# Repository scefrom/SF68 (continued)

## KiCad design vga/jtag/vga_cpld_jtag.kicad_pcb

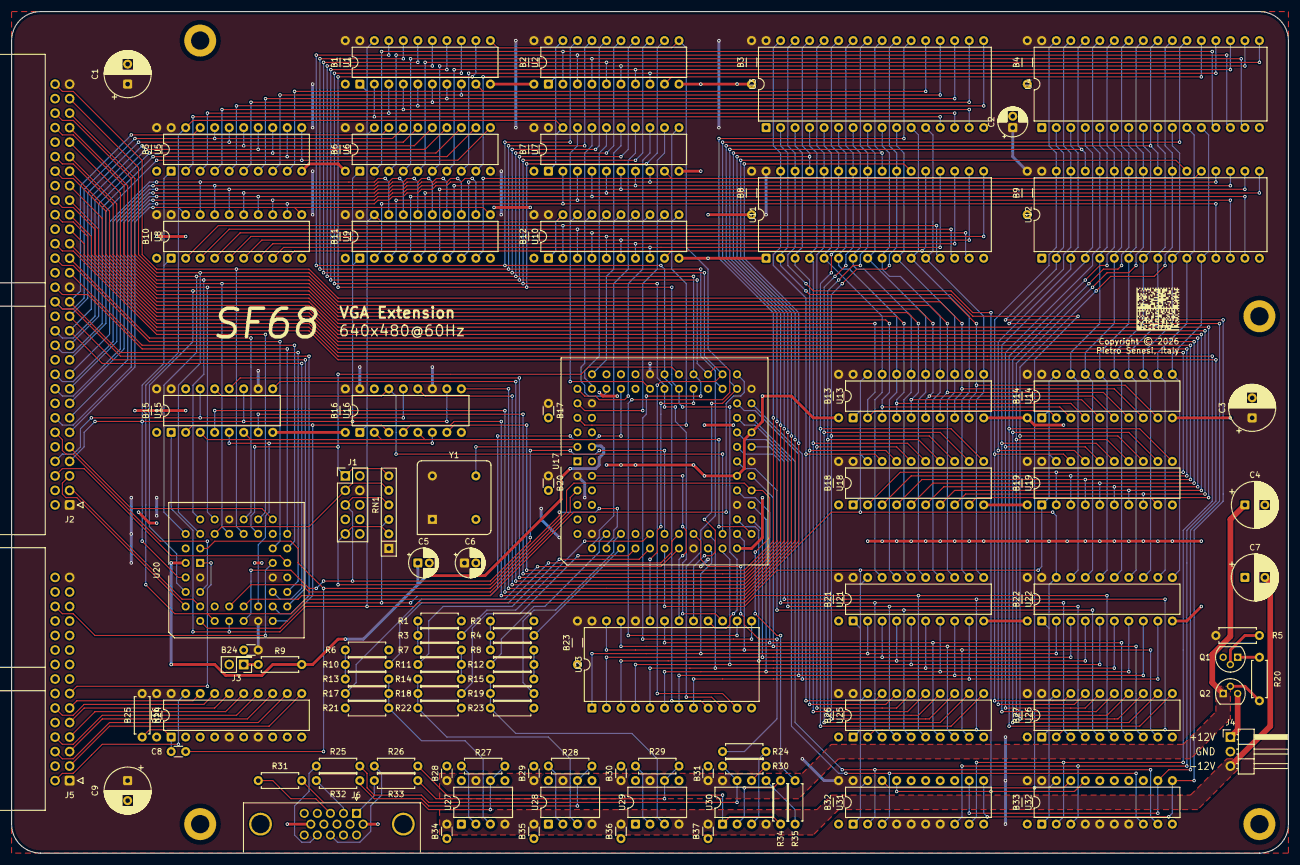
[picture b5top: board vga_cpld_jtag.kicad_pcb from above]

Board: 2 copper layers, 223.5 x 147.3 mm, 127 parts (0 on the bottom side), 229 nets.

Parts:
B1, B2, B3, B4, B5, B6, B7, B8, B9, B10, B11, B12, B13, B14, B15, B16, B18, B19, B21, B22, B23, B25, B26, B27, B32, B33: 100n; C_Disc_D3.0mm_W1.6mm_P7.62mm
B17, B20, B24, B28, B29, B30, B31, B34, B35, B36, B37: 100n; C_Disc_D3.0mm_W1.6mm_P2.54mm
C1, C3, C4, C7, C9: 100u; CP_Radial_D8.0mm_P3.50mm
C2, C5, C6: 10u; CP_Radial_D5.0mm_P2.00mm
C8: 22p; C_Disc_D3.0mm_W1.6mm_P2.54mm
J1: jtag; PinHeader_2x05_P2.54mm_Vertical
J2: perslota; IDC-Header_2x30_P2.54mm_Horizontal
J3: oe1_12v_bypass; PinHeader_2x01_P2.54mm_Vertical
J4: vgasupply; PinHeader_1x03_P2.54mm_Horizontal
J5: perslotb; IDC-Header_2x15_P2.54mm_Horizontal
J6: DE15_Socket_HighDensity; DSUB-15-HD_Socket_Horizontal_P2.29x1.90mm_EdgePinOffset3.03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
M1, M2, M3, M4: MountingHole_3.2mm_M3_DIN965_Pad
Q1: Q_NPN_CBE; TO-92
Q2: Q_PNP_CBE; TO-92
R1, R2, R3, R4, R6, R10, R11, R12, R17, R18, R19, R20: 5.4k; R_Axial_DIN0207_L6.3mm_D2.5mm_P7.62mm_Horizontal
R5: 10k; R_Axial_DIN0207_L6.3mm_D2.5mm_P7.62mm_Horizontal
R7, R8, R13, R14, R15: 2.7k; R_Axial_DIN0207_L6.3mm_D2.5mm_P7.62mm_Horizontal
R9, R24, R30, R34, R35: 1k; R_Axial_DIN0207_L6.3mm_D2.5mm_P7.62mm_Horizontal
R16: 4.7k; R_Axial_DIN0207_L6.3mm_D2.5mm_P7.62mm_Horizontal
R21, R22, R23: 800; R_Axial_DIN0207_L6.3mm_D2.5mm_P7.62mm_Horizontal
R25, R26: 50; R_Axial_DIN0207_L6.3mm_D2.5mm_P7.62mm_Horizontal
R27, R28, R29: 620; R_Axial_DIN0207_L6.3mm_D2.5mm_P7.62mm_Horizontal
R31, R32, R33: 33; R_Axial_DIN0207_L6.3mm_D2.5mm_P7.62mm_Horizontal
RN1: 10k; R_Array_SIP6
U1, U2, U7, U10, U13, U14, U18, U19, U21, U22, U25, U26, U31, U32: 74AHC541; DIP-20_W7.62mm
U3, U4, U11, U12: AS6C4008-55PCN; DIP-32_W15.24mm
U5, U6, U8, U9: 74HC245; DIP-20_W7.62mm
U15, U16: 74HC157; DIP-16_W7.62mm
U17: ATF1508AS-xJx84; PLCC-84_THT-Socket
U20: ATF1502AS-xJx44; PLCC-44_THT-Socket
U23: AT28C16; DIP-24_W15.24mm
U24: 74HC541; DIP-20_W7.62mm
U27, U28, U29: LM6171xxN; DIP-8_W7.62mm
U30: LM6172; DIP-8_W7.62mm
Y1: CXO_DIP8_25.175MHz; Oscillator_DIP-8

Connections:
+5V: B1.1, B2.1, B3.1, B4.1, B5.1, B6.1, B7.1, B8.1, B9.1, B10.1, B11.1, B12.1, B13.1, B14.1, B15.1, B16.1, B17.1, B18.1, B19.1, B20.1, B21.1, B22.1, B23.1, B24.1, B25.1, B26.1, B27.1, B32.1, B33.1, C1.1, C2.1, C3.1, C6.1, C9.1, J1.4, J2.1, J2.31, J2.59, J5.1, J5.29, R5.1, R16.1, RN1.1 (common), U1.20 (VCC), U2.20 (VCC), U3.32 (VCC), U4.32 (VCC), U5.20 (VCC), U6.20 (VCC), U7.20 (VCC), U8.20 (VCC), U9.20 (VCC), U10.20 (VCC), U11.32 (VCC), U12.32 (VCC), U13.20 (VCC), U14.20 (VCC), U15.10 (I1c), U15.16 (VCC), U16.11 (I0c), U16.16 (VCC), U17.3 (VCC_INT), U17.13 (VCC_IO), U17.26 (VCC_IO), U17.38 (VCC_IO), U17.43 (VCC_INT), U17.53 (VCC_IO), U17.66 (VCC_IO), U17.78 (VCC_IO), U18.20 (VCC), U19.20 (VCC), U20.3 (VCC), U20.15 (VCC), U20.23 (VCC), U20.35 (VCC), U21.20 (VCC), U22.20 (VCC), U23.21 (~WE), U23.24 (VCC), U24.5 (A3), U24.7 (A5), U24.20 (VCC), U25.20 (VCC), U26.20 (VCC), U31.4 (A2), U31.5 (A3), U31.6 (A4), U31.7 (A5), U31.20 (VCC), U32.4 (A2), U32.5 (A3), U32.6 (A4), U32.7 (A5), U32.20 (VCC), Y1.1 (EN), Y1.8 (Vcc)
/08to02: RN1.3 (R2), U17.71 (I/O/TDO), U20.7 (I/O/TDI)
/AC.~P: J5.26, U20.25 (I/O/PD2)
/ADR_{0}: U17.51 (I/O), U21.9 (A7), U22.9 (A7), U23.8 (A0)
/ADR_{1}: U17.52 (I/O), U21.8 (A6), U22.8 (A6), U23.7 (A1)
/ADR_{2}: U17.37 (I/O), U21.7 (A5), U22.7 (A5), U23.6 (A2)
/ADR_{3}: U17.29 (I/O), U21.6 (A4), U22.6 (A4), U23.5 (A3)
/ADR_{4}: U17.30 (I/O), U21.5 (A3), U22.5 (A3), U23.4 (A4)
/ADR_{5}: U17.36 (I/O), U21.4 (A2), U22.4 (A2), U23.3 (A5)
/ADR_{6}: U17.35 (I/O), U21.3 (A1), U22.3 (A1), U23.2 (A6)
/ADR_{7}: U17.28 (I/O), U21.2 (A0), U22.2 (A0), U23.1 (A7)
/ADR_{8}: U17.34 (I/O), U23.23 (A8), U25.9 (A7), U26.9 (A7)
/ADR_{9}: U17.41 (I/O), U23.22 (A9), U25.8 (A6), U26.8 (A6)
/ADR_{10}: U17.40 (I/O), U23.19 (A10), U25.7 (A5), U26.7 (A5)
/ADR_{11}: U17.22 (I/O), U25.6 (A4), U26.6 (A4)
/ADR_{12}: U17.44 (I/O), U25.5 (A3), U26.5 (A3)
/ADR_{13}: U17.48 (I/O), U25.4 (A2), U26.4 (A2)
/ADR_{14}: U17.46 (I/O), U25.3 (A1), U26.3 (A1)
/ADR_{15}: U17.45 (I/O/PD2), U25.2 (A0), U26.2 (A0)
/ADR_{16}: U17.49 (I/O), U31.2 (A0), U32.9 (A7)
/ADR_{17}: U17.50 (I/O), U31.3 (A1), U32.8 (A6)
/A_{1}: J2.60, U13.9 (A7), U14.9 (A7), U20.34 (I/O)
/A_{2}: J2.57, U13.8 (A6), U14.8 (A6), U20.41 (I/O/GCLK3)
/A_{3}: J2.55, U13.7 (A5), U14.7 (A5), U20.40 (I/O)
/A_{4}: J2.56, U13.6 (A4), U14.6 (A4), U20.39 (I/O)
/A_{5}: J2.53, U13.5 (A3), U14.5 (A3), U20.36 (I/O)
/A_{6}: J2.54, U13.4 (A2), U14.4 (A2), U20.37 (I/O)
/A_{7}: J2.51, U13.3 (A1), U14.3 (A1), U20.4 (I/O)
/A_{8}: J2.49, U13.2 (A0), U14.2 (A0)
/A_{9}: J2.50, U18.9 (A7), U19.9 (A7)
/A_{10}: J2.47, U18.8 (A6), U19.8 (A6)
/A_{11}: J2.48, U18.7 (A5), U19.7 (A5)
/A_{12}: J2.45, U18.6 (A4), U19.6 (A4)
/A_{13}: J2.43, U18.5 (A3), U19.5 (A3)
/A_{14}: J2.44, U18.4 (A2), U19.4 (A2)
/A_{15}: J2.41, U18.3 (A1), U19.3 (A1)
/A_{16}: J2.42, U18.2 (A0), U19.2 (A0)
/A_{17}: J2.39, U31.9 (A7), U32.2 (A0)
/A_{18}: J2.37, U31.8 (A6), U32.3 (A1)
/A_{19}: J2.38, U20.31 (I/O)
/A_{20}: J2.35, U20.33 (I/O)
/A_{21}: J2.36, U20.27 (I/O)
/A_{22}: J2.33, U20.26 (I/O)
/A_{23}: J2.32, U20.28 (I/O)
/BE.~IO: J2.12, U20.5 (I/O)
/BE.~M: J2.9, U20.29 (I/O)
/CLK: U17.83 (I/GCLK1), Y1.5 (OUT)
/CM: U17.5 (I/O), U20.12 (I/O)
/DAT_{0}: U1.18 (Y0), U2.18 (Y0), U17.64 (I/O), U23.9 (D0)
/DAT_{1}: U1.17 (Y1), U2.17 (Y1), U17.57 (I/O), U23.10 (D1)
/DAT_{2}: U1.16 (Y2), U2.16 (Y2), U17.56 (I/O), U23.11 (D2)
/DAT_{3}: U1.15 (Y3), U2.15 (Y3), U17.60 (I/O), U23.13 (D3)
/DAT_{4}: U1.14 (Y4), U2.14 (Y4), U17.58 (I/O), U23.14 (D4)
/DAT_{5}: U1.13 (Y5), U2.13 (Y5), U17.65 (I/O), U23.15 (D5)
/DAT_{6}: U1.12 (Y6), U2.12 (Y6), U17.63 (I/O), U23.16 (D6)
/DAT_{7}: U1.11 (Y7), U2.11 (Y7), U17.55 (I/O), U23.17 (D7)
/DAT_{8}: U7.18 (Y0), U10.18 (Y0), U17.67 (I/O)
/DAT_{9}: U7.17 (Y1), U10.17 (Y1), U17.73 (I/O)
/DAT_{10}: U7.16 (Y2), U10.16 (Y2), U17.76 (I/O)
/DAT_{11}: U7.15 (Y3), U10.15 (Y3), U17.74 (I/O)
/DAT_{12}: U7.14 (Y4), U10.14 (Y4), U17.12 (I/O/PD1)
/DAT_{13}: U7.13 (Y5), U10.13 (Y5), U17.75 (I/O)
/DAT_{14}: U7.12 (Y6), U10.12 (Y6), U17.77 (I/O)
/DAT_{15}: U7.11 (Y7), U10.11 (Y7), U17.79 (I/O)
/DIR.~R: J2.8, U15.14 (I0d), U16.13 (I1d)
/DIR.~W: J2.7, U5.1 (A->B), U6.1 (A->B), U8.1 (A->B), U9.1 (A->B), U15.11 (I0c), U16.10 (I1c), U20.2 (I/GCLK2/OE2)
/DS.~L: J2.6, U20.24 (I/O)
/DS.~U: J2.5, U20.6 (I/O)
/D_{0}: J2.29, U5.18 (B0), U6.18 (B0), U20.20 (I/O)
/D_{1}: J2.30, U5.17 (B1), U6.17 (B1), U20.19 (I/O)
/D_{2}: J2.27, U5.16 (B2), U6.16 (B2), U20.18 (I/O)
/D_{3}: J2.25, U5.15 (B3), U6.15 (B3), U20.21 (I/O)
/D_{4}: J2.26, U5.14 (B4), U6.14 (B4)
/D_{5}: J2.23, U5.13 (B5), U6.13 (B5)
/D_{6}: J2.24, U5.12 (B6), U6.12 (B6)
/D_{7}: J2.21, U5.11 (B7), U6.11 (B7)
/D_{8}: J2.19, U8.18 (B0), U9.18 (B0)
/D_{9}: J2.20, U8.17 (B1), U9.17 (B1)
/D_{10}: J2.17, U8.16 (B2), U9.16 (B2)
/D_{11}: J2.18, U8.15 (B3), U9.15 (B3)
/D_{12}: J2.15, U8.14 (B4), U9.14 (B4)
/D_{13}: J2.13, U8.13 (B5), U9.13 (B5)
/D_{14}: J2.14, U8.12 (B6), U9.12 (B6)
/D_{15}: J2.11, U8.11 (B7), U9.11 (B7)
/IBSY: J5.2, U24.19 (G2)
/IRQ_{0}: J5.11, U24.18 (Y0)
/IRQ_{1}: J5.12, U24.17 (Y1)
/IRQ_{2}: J5.9, U24.16 (Y2)
/IRQ_{3}: J5.7, U24.15 (Y3)
/IRQ_{4}: J5.8, U24.14 (Y4)
/IRQ_{5}: J5.5, U24.13 (Y5)
/IRQ_{6}: J5.6, U24.12 (Y6)
/IRQ_{7}: J5.3, U24.11 (Y7)
/JTAG.TCK: J1.1, RN1.6 (R5), U17.62 (I/O/TCK), U20.32 (I/O/TCK)
/JTAG.TDI: J1.9, RN1.2 (R1), U17.14 (I/O/TDI)
/JTAG.TDO: J1.3, RN1.5 (R4), U20.38 (I/O/TDO)
/JTAG.TMS: J1.5, RN1.4 (R3), U17.23 (I/O/TMS), U20.13 (I/O/TMS)
/RGB_{0}: R10.1, U17.25 (I/O)
/RGB_{1}: R17.1, U17.24 (I/O)
/RGB_{2}: R3.1, U17.21 (I/O)
/RGB_{3}: R11.1, U17.20 (I/O/PD)
/RGB_{4}: R18.1, U17.18 (I/O)
/RGB_{5}: R4.1, U17.16 (I/O)
/RGB_{6}: R12.1, U17.15 (I/O)
/RGB_{7}: R19.1, U17.17 (I/O)
/UP: U17.54 (I/O), U20.14 (I/O)
/VBS: U1.1 (G1), U1.19 (G2), U6.19 (CE), U9.19 (CE), U10.1 (G1), U10.19 (G2), U14.1 (G1), U14.19 (G2), U15.1 (S), U16.1 (S), U19.1 (G1), U19.19 (G2), U20.11 (I/O/PD1), U21.1 (G1), U21.19 (G2), U25.1 (G1), U25.19 (G2), U31.1 (G1), U31.19 (G2)
/VB_{0}A_{0}: U3.12 (A0), U11.12 (A0), U13.11 (Y7), U21.11 (Y7)
/VB_{0}A_{1}: U3.11 (A1), U11.11 (A1), U13.12 (Y6), U21.12 (Y6)
/VB_{0}A_{2}: U3.10 (A2), U11.10 (A2), U13.13 (Y5), U21.13 (Y5)
/VB_{0}A_{3}: U3.9 (A3), U11.9 (A3), U13.14 (Y4), U21.14 (Y4)
/VB_{0}A_{4}: U3.8 (A4), U11.8 (A4), U13.15 (Y3), U21.15 (Y3)
/VB_{0}A_{5}: U3.7 (A5), U11.7 (A5), U13.16 (Y2), U21.16 (Y2)
/VB_{0}A_{6}: U3.6 (A6), U11.6 (A6), U13.17 (Y1), U21.17 (Y1)
/VB_{0}A_{7}: U3.5 (A7), U11.5 (A7), U13.18 (Y0), U21.18 (Y0)
/VB_{0}A_{8}: U3.27 (A8), U11.27 (A8), U18.11 (Y7), U25.11 (Y7)
/VB_{0}A_{9}: U3.26 (A9), U11.26 (A9), U18.12 (Y6), U25.12 (Y6)
/VB_{0}A_{10}: U3.23 (A10), U11.23 (A10), U18.13 (Y5), U25.13 (Y5)
/VB_{0}A_{11}: U3.25 (A11), U11.25 (A11), U18.14 (Y4), U25.14 (Y4)
/VB_{0}A_{12}: U3.4 (A12), U11.4 (A12), U18.15 (Y3), U25.15 (Y3)
/VB_{0}A_{13}: U3.28 (A13), U11.28 (A13), U18.16 (Y2), U25.16 (Y2)
/VB_{0}A_{14}: U3.3 (A14), U11.3 (A14), U18.17 (Y1), U25.17 (Y1)
/VB_{0}A_{15}: U3.31 (A15), U11.31 (A15), U18.18 (Y0), U25.18 (Y0)
/VB_{0}A_{16}: U3.2 (A16), U11.2 (A16), U31.18 (Y0), U32.18 (Y0)
/VB_{0}A_{17}: U3.30 (A17), U11.30 (A17), U31.17 (Y1), U32.17 (Y1)
/VB_{0}C.~E_{L}: U3.22 (CE#), U16.7 (Zb)
/VB_{0}C.~E_{U}: U11.22 (CE#), U16.4 (Za)
/VB_{0}C.~R: U3.24 (OE#), U11.24 (OE#), U16.12 (Zd)
/VB_{0}C.~W: U3.29 (WE#), U11.29 (WE#), U16.9 (Zc)
/VB_{0}D_{0}: U1.2 (A0), U3.13 (DQ0), U5.2 (A0)
/VB_{0}D_{1}: U1.3 (A1), U3.14 (DQ1), U5.3 (A1)
/VB_{0}D_{2}: U1.4 (A2), U3.15 (DQ2), U5.4 (A2)
/VB_{0}D_{3}: U1.5 (A3), U3.17 (DQ3), U5.5 (A3)
/VB_{0}D_{4}: U1.6 (A4), U3.18 (DQ4), U5.6 (A4)
/VB_{0}D_{5}: U1.7 (A5), U3.19 (DQ5), U5.7 (A5)
/VB_{0}D_{6}: U1.8 (A6), U3.20 (DQ6), U5.8 (A6)
/VB_{0}D_{7}: U1.9 (A7), U3.21 (DQ7), U5.9 (A7)
/VB_{0}D_{8}: U8.2 (A0), U10.2 (A0), U11.13 (DQ0)
/VB_{0}D_{9}: U8.3 (A1), U10.3 (A1), U11.14 (DQ1)
/VB_{0}D_{10}: U8.4 (A2), U10.4 (A2), U11.15 (DQ2)
/VB_{0}D_{11}: U8.5 (A3), U10.5 (A3), U11.17 (DQ3)
/VB_{0}D_{12}: U8.6 (A4), U10.6 (A4), U11.18 (DQ4)
/VB_{0}D_{13}: U8.7 (A5), U10.7 (A5), U11.19 (DQ5)
/VB_{0}D_{14}: U8.8 (A6), U10.8 (A6), U11.20 (DQ6)
/VB_{0}D_{15}: U8.9 (A7), U10.9 (A7), U11.21 (DQ7)
/VB_{1}A_{0}: U4.12 (A0), U12.12 (A0), U14.11 (Y7), U22.11 (Y7)
/VB_{1}A_{1}: U4.11 (A1), U12.11 (A1), U14.12 (Y6), U22.12 (Y6)
/VB_{1}A_{2}: U4.10 (A2), U12.10 (A2), U14.13 (Y5), U22.13 (Y5)
/VB_{1}A_{3}: U4.9 (A3), U12.9 (A3), U14.14 (Y4), U22.14 (Y4)
/VB_{1}A_{4}: U4.8 (A4), U12.8 (A4), U14.15 (Y3), U22.15 (Y3)
/VB_{1}A_{5}: U4.7 (A5), U12.7 (A5), U14.16 (Y2), U22.16 (Y2)
/VB_{1}A_{6}: U4.6 (A6), U12.6 (A6), U14.17 (Y1), U22.17 (Y1)
/VB_{1}A_{7}: U4.5 (A7), U12.5 (A7), U14.18 (Y0), U22.18 (Y0)
/VB_{1}A_{8}: U4.27 (A8), U12.27 (A8), U19.11 (Y7), U26.11 (Y7)
/VB_{1}A_{9}: U4.26 (A9), U12.26 (A9), U19.12 (Y6), U26.12 (Y6)
/VB_{1}A_{10}: U4.23 (A10), U12.23 (A10), U19.13 (Y5), U26.13 (Y5)
/VB_{1}A_{11}: U4.25 (A11), U12.25 (A11), U19.14 (Y4), U26.14 (Y4)
/VB_{1}A_{12}: U4.4 (A12), U12.4 (A12), U19.15 (Y3), U26.15 (Y3)
/VB_{1}A_{13}: U4.28 (A13), U12.28 (A13), U19.16 (Y2), U26.16 (Y2)
/VB_{1}A_{14}: U4.3 (A14), U12.3 (A14), U19.17 (Y1), U26.17 (Y1)
/VB_{1}A_{15}: U4.31 (A15), U12.31 (A15), U19.18 (Y0), U26.18 (Y0)
/VB_{1}A_{16}: U4.2 (A16), U12.2 (A16), U31.11 (Y7), U32.11 (Y7)
/VB_{1}A_{17}: U4.30 (A17), U12.30 (A17), U31.12 (Y6), U32.12 (Y6)
/VB_{1}C.~E_{L}: U4.22 (CE#), U15.7 (Zb)
/VB_{1}C.~E_{U}: U12.22 (CE#), U15.4 (Za)
/VB_{1}C.~R: U4.24 (OE#), U12.24 (OE#), U15.12 (Zd)
/VB_{1}C.~W: U4.29 (WE#), U12.29 (WE#), U15.9 (Zc)
/VB_{1}D_{0}: U2.2 (A0), U4.13 (DQ0), U6.2 (A0)
/VB_{1}D_{1}: U2.3 (A1), U4.14 (DQ1), U6.3 (A1)
/VB_{1}D_{2}: U2.4 (A2), U4.15 (DQ2), U6.4 (A2)
/VB_{1}D_{3}: U2.5 (A3), U4.17 (DQ3), U6.5 (A3)
/VB_{1}D_{4}: U2.6 (A4), U4.18 (DQ4), U6.6 (A4)
/VB_{1}D_{5}: U2.7 (A5), U4.19 (DQ5), U6.7 (A5)
/VB_{1}D_{6}: U2.8 (A6), U4.20 (DQ6), U6.8 (A6)
/VB_{1}D_{7}: U2.9 (A7), U4.21 (DQ7), U6.9 (A7)
/VB_{1}D_{8}: U7.2 (A0), U9.2 (A0), U12.13 (DQ0)
/VB_{1}D_{9}: U7.3 (A1), U9.3 (A1), U12.14 (DQ1)
/VB_{1}D_{10}: U7.4 (A2), U9.4 (A2), U12.15 (DQ2)
/VB_{1}D_{11}: U7.5 (A3), U9.5 (A3), U12.17 (DQ3)
/VB_{1}D_{12}: U7.6 (A4), U9.6 (A4), U12.18 (DQ4)
/VB_{1}D_{13}: U7.7 (A5), U9.7 (A5), U12.19 (DQ5)
/VB_{1}D_{14}: U7.8 (A6), U9.8 (A6), U12.20 (DQ6)
/VB_{1}D_{15}: U7.9 (A7), U9.9 (A7), U12.21 (DQ7)
/vga_interface/BLUE: J6.3, R31.2
/vga_interface/GREEN: J6.2, R32.2
/vga_interface/RED: J6.1, R33.2
/vga_interface/~HSYNC: J6.13, R26.2
/vga_interface/~VSYNC: J6.14, R25.2
/~BE_{L}: U15.5 (I0b), U16.6 (I1b), U20.16 (I/O)
/~BE_{U}: U15.2 (I0a), U16.3 (I1a), U20.17 (I/O)
/~CME: U17.4 (I/O), U23.18 (~CE)
/~CMO: U17.61 (I/O), U23.20 (~OE)
/~HS: R24.1, U17.27 (I/O)
/~RES: J5.13, U20.1 (I/GCLR)
/~RIH: J2.3, U20.8 (I/O)
/~VBS: U2.1 (G1), U2.19 (G2), U5.19 (CE), U7.1 (G1), U7.19 (G2), U8.19 (CE), U13.1 (G1), U13.19 (G2), U18.1 (G1), U18.19 (G2), U20.9 (I/O), U22.1 (G1), U22.19 (G2), U26.1 (G1), U26.19 (G2), U32.1 (G1), U32.19 (G2)
/~VME: U15.3 (I1a), U15.6 (I1b), U16.2 (I0a), U16.5 (I0b), U17.33 (I/O)
/~VMO: U15.13 (I1d), U16.14 (I0d), U17.31 (I/O)
/~VS: C8.2, R35.1, U17.39 (I/O), U20.43 (I/GCLK1)
GND: B1.2, B2.2, B3.2, B4.2, B5.2, B6.2, B7.2, B8.2, B9.2, B10.2, B11.2, B12.2, B13.2, B14.2, B15.2, B16.2, B17.2, B18.2, B19.2, B20.2, B21.2, B22.2, B23.2, B24.2, B25.2, B26.2, B27.2, B28.2, B29.2, B30.2, B31.2, B32.2, B33.2, B34.1, B35.1, B36.1, B37.1, C1.2, C2.2, C3.2, C4.2, C5.2, C6.2, C7.1, C9.2, J1.2, J1.10, J2.4, J2.10, J2.16, J2.22, J2.28, J2.34, J2.40, J2.46, J2.52, J2.58, J3.2, J4.2, J5.4, J5.10, J5.16, J5.21, J5.22, J5.28, J6.5, J6.6, J6.7, J6.8, J6.10, M1.1, M2.1, M3.1, M4.1, Q1.3 (E), R1.1, R2.1, R6.1, R21.1, R22.1, R23.1, U1.10 (GND), U2.10 (GND), U3.1 (A18), U3.16 (VSS), U4.1 (A18), U4.16 (VSS), U5.10 (GND), U6.10 (GND), U7.10 (GND), U8.10 (GND), U9.10 (GND), U10.10 (GND), U11.1 (A18), U11.16 (VSS), U12.1 (A18), U12.16 (VSS), U13.10 (GND), U14.10 (GND), U15.8 (GND), U15.15 (E), U16.8 (GND), U16.15 (E), U17.7 (GND), U17.19 (GND), U17.32 (GND), U17.42 (GND), U17.47 (GND), U17.59 (GND), U17.72 (GND), U17.82 (GND), U18.10 (GND), U19.10 (GND), U20.10 (GND), U20.22 (GND), U20.30 (GND), U20.42 (GND), U21.10 (GND), U22.10 (GND), U23.12 (GND), U24.2 (A0), U24.3 (A1), U24.4 (A2), U24.6 (A4), U24.8 (A6), U24.9 (A7), U24.10 (GND), U25.10 (GND), U26.10 (GND), U31.10 (GND), U32.10 (GND), Y1.4 (GND)
unnamed: J3.1, R9.1
unnamed: J4.1, Q2.3 (E)
unnamed: Q1.2 (B), R5.2
unnamed: Q1.1 (C), R20.2
unnamed: Q2.2 (B), R20.1
unnamed: R1.2, R3.2, R7.1
unnamed: R2.2, R4.2, R8.1
unnamed: R6.2, R10.2, R13.1
unnamed: R7.2, R11.2, R14.1
unnamed: R8.2, R12.2, R15.1
unnamed: R25.1, R30.2, U30.7
unnamed: R26.1, R34.2, U30.1
unnamed: R27.2, R31.1, U27.6
unnamed: R28.2, R32.1, U28.6
unnamed: R29.2, R33.1, U29.6
unnamed: C8.1, R16.2, U24.1 (G1)
unnamed: R13.2, R17.2, R21.2, U27.3 (+)
unnamed: R27.1, U27.2 (-)
unnamed: R14.2, R18.2, R22.2, U28.3 (+)
unnamed: R28.1, U28.2 (-)
unnamed: R15.2, R19.2, R23.2, U29.3 (+)
unnamed: R29.1, U29.2 (-)
unnamed: R24.2, U30.3 (+)
unnamed: R34.1, U30.2 (-)
unnamed: R35.2, U30.5 (+)
unnamed: R30.1, U30.6 (-)
OE1_+12V: C5.1, R9.2, U17.84 (I/OE1), U20.44 (I/OE1)
VCC_VGA+: B28.1, B29.1, B30.1, B31.1, C4.1, Q2.1 (C), U27.7 (V+), U28.7 (V+), U29.7 (V+), U30.8 (V+)
VCC_VGA-: B34.2, B35.2, B36.2, B37.2, C7.2, J4.3, U27.4 (V-), U28.4 (V-), U29.4 (V-), U30.4 (V-)

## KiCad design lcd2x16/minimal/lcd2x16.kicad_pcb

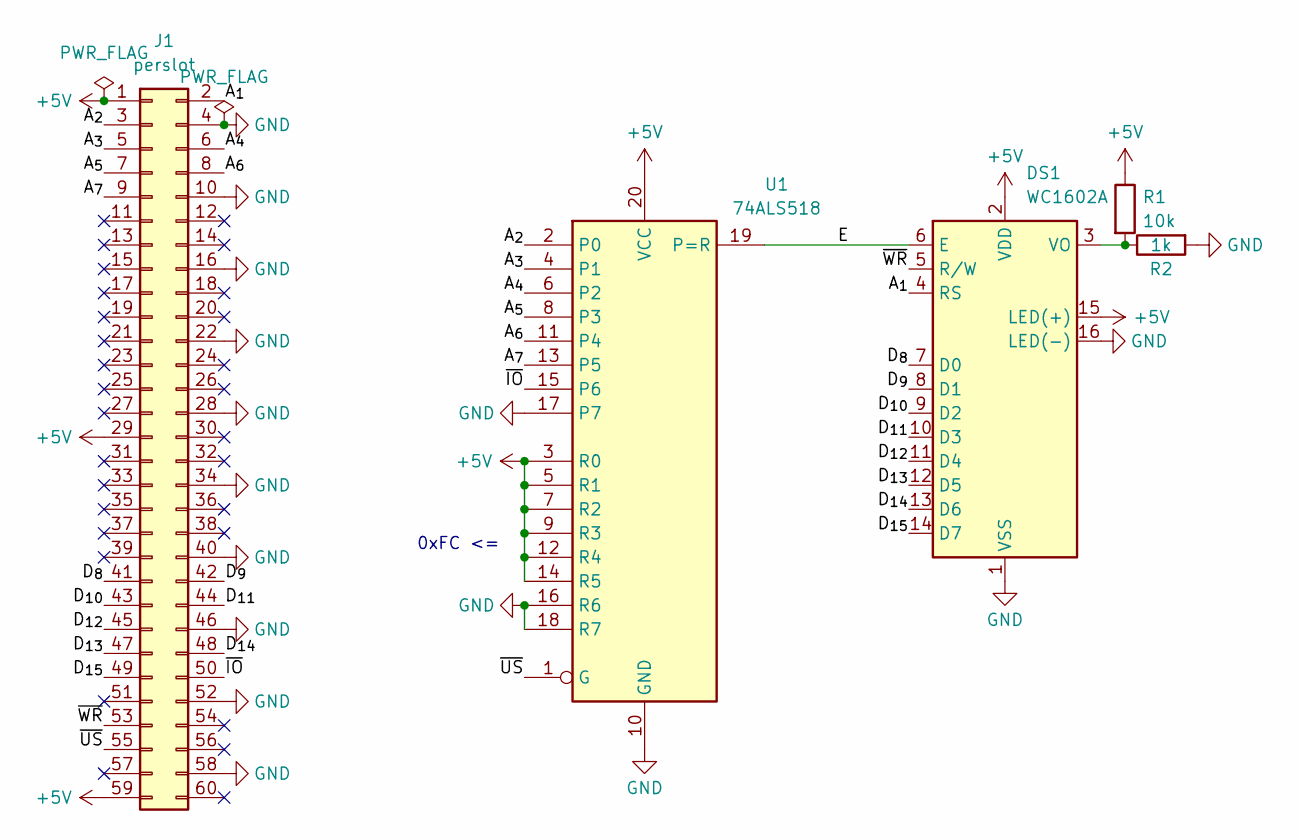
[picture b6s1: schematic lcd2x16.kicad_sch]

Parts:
DS1: WC1602A
J1: perslot; IDC-Header_2x30_P2.54mm_Horizontal
R1: 10k; R_Axial_DIN0207_L6.3mm_D2.5mm_P7.62mm_Horizontal
R2: 1k; R_Axial_DIN0207_L6.3mm_D2.5mm_P7.62mm_Horizontal
U1: 74ALS518; DIP-20_W7.62mm

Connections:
+5V: DS1.2 (VDD), DS1.15 (LED(+)), J1.1, J1.29, J1.59, R1.1, U1.3 (R0), U1.5 (R1), U1.7 (R2), U1.9 (R3), U1.12 (R4), U1.14 (R5), U1.20 (VCC)
/A_{1}: DS1.4 (RS), J1.2
/A_{2}: J1.3, U1.2 (P0)
/A_{3}: J1.5, U1.4 (P1)
/A_{4}: J1.6, U1.6 (P2)
/A_{5}: J1.7, U1.8 (P3)
/A_{6}: J1.8, U1.11 (P4)
/A_{7}: J1.9, U1.13 (P5)
/D_{8}: DS1.7 (D0), J1.41
/D_{9}: DS1.8 (D1), J1.42
/D_{10}: DS1.9 (D2), J1.43
/D_{11}: DS1.10 (D3), J1.44
/D_{12}: DS1.11 (D4), J1.45
/D_{13}: DS1.12 (D5), J1.47
/D_{14}: DS1.13 (D6), J1.48
/D_{15}: DS1.14 (D7), J1.49
/E: DS1.6 (E), U1.19 (P=R)
/~IO: J1.50, U1.15 (P6)
/~US: J1.55, U1.1 (G)
/~WR: DS1.5 (R/W), J1.53
GND: DS1.1 (VSS), DS1.16 (LED(-)), J1.4, J1.10, J1.16, J1.22, J1.28, J1.34, J1.40, J1.46, J1.52, J1.58, R2.2, U1.10 (GND), U1.16 (R6), U1.17 (P7), U1.18 (R7)
unnamed: DS1.3 (VO), R1.2, R2.1

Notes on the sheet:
0xFC <=

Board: 2 copper layers, 5 parts (0 on the bottom side), 22 nets, no tracks yet.

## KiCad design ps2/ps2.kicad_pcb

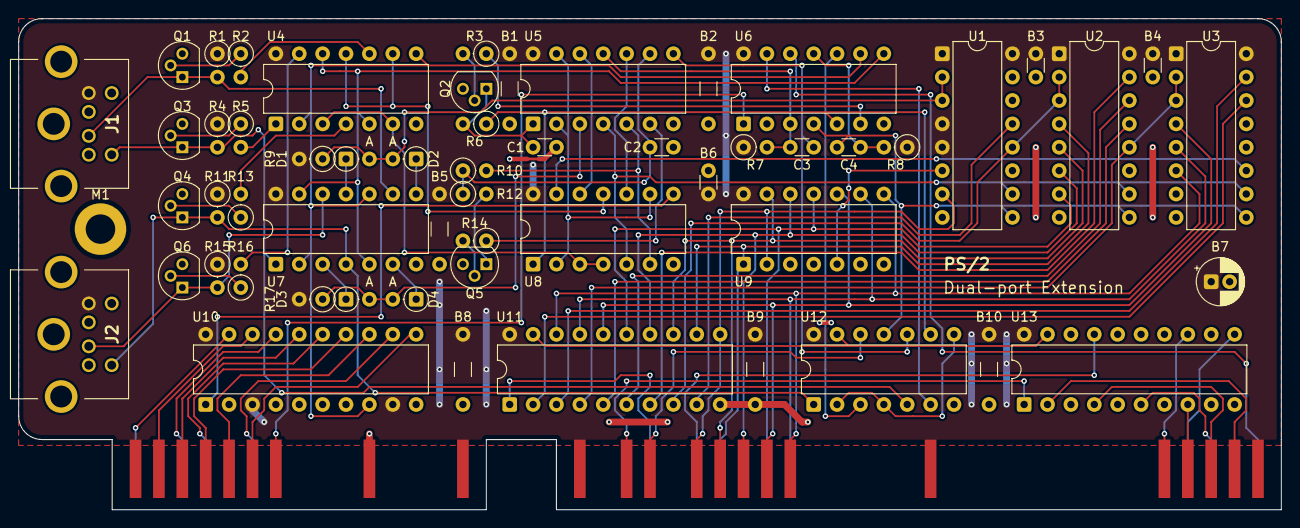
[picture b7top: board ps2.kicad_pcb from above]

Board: 2 copper layers, 137.2 x 53.3 mm, 59 parts (0 on the bottom side), 85 nets.

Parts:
B1, B2, B5, B8, B9, B10: 100n; C_Disc_D3.0mm_W1.6mm_P7.62mm
B3, B4, B6: 100n; C_Disc_D3.0mm_W1.6mm_P2.54mm
B7: 10u; CP_Radial_D5.0mm_P2.00mm
C1, C2: 10n; C_Disc_D3.0mm_W1.6mm_P2.54mm
C3: 220p; C_Disc_D3.0mm_W1.6mm_P2.54mm
C4: 22p; C_Disc_D3.0mm_W1.6mm_P2.54mm
D1, D2, D3, D4: schotty; D_DO-35_SOD27_P2.54mm_Vertical_AnodeUp
J1: port0; 57492651
J2: port1; 57492651
J3: perslot1b; edge_connector_15p_2.54mm
J4: perslot1a; edge_connector_30p_2.54mm
M1: MountingHole_3.2mm_M3_DIN965_Pad
Q1, Q2, Q3, Q4, Q5, Q6: BC547B; TO-92
R1, R4, R11, R15: 4k7; R_Axial_DIN0207_L6.3mm_D2.5mm_P2.54mm_Vertical
R2, R3, R5, R9, R10, R13, R14, R16, R17: 10k; R_Axial_DIN0207_L6.3mm_D2.5mm_P2.54mm_Vertical
R6: 14k7; R_Axial_DIN0207_L6.3mm_D2.5mm_P2.54mm_Vertical
R7, R12: 1k; R_Axial_DIN0207_L6.3mm_D2.5mm_P2.54mm_Vertical
R8: 2k; R_Axial_DIN0207_L6.3mm_D2.5mm_P2.54mm_Vertical
U1, U2, U3: 74HC195; DIP-16_W7.62mm
U4: 74HC02; DIP-14_W7.62mm
U5: 74HC14; DIP-14_W7.62mm
U6: 74HC74; DIP-14_W7.62mm
U7, U12: 74HC32; DIP-14_W7.62mm
U8: 74HC00; DIP-14_W7.62mm
U9: 74HC280; DIP-14_W7.62mm
U10, U11: 74HC541; DIP-20_W7.62mm
U13: 74HC688; DIP-20_W7.62mm

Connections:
+5V: B1.1, B2.1, B3.1, B4.1, B5.1, B6.1, B7.1, B8.1, B9.1, B10.1, J1.4, J2.4, J3.1, J3.29, J4.1, J4.31, J4.59, R1.1, R4.1, R7.1, R8.1, R9.2, R11.1, R15.1, R17.2, U1.1 (~MR), U1.4 (P0), U1.5 (P1), U1.16 (VCC), U2.1 (~MR), U2.16 (VCC), U3.1 (~MR), U3.16 (VCC), U4.14 (VCC), U5.14 (VCC), U6.14 (VCC), U7.14 (VCC), U8.14 (VCC), U9.14 (VCC), U10.3 (A1), U10.9 (A7), U10.20 (VCC), U11.20 (VCC), U12.14 (VCC), U13.20 (VCC)
/A_{1}: J4.60, U6.12 (D)
/A_{2}: J4.57, U13.2 (P0)
/A_{3}: J4.55, U13.4 (P1)
/A_{4}: J4.56, U13.6 (P2)
/A_{5}: J4.53, U13.8 (P3)
/A_{6}: J4.54, U13.11 (P4)
/A_{7}: J4.51, U13.13 (P5)
/BE.~IO: J4.12, U13.17 (P7)
/CP: U1.10 (CP), U2.10 (CP), U3.10 (CP), U5.4, U8.5
/DAT_{0}: J1.1, Q1.1 (C), R1.2, U7.9
/DAT_{1}: J2.1, Q6.1 (C), R15.2, U7.12
/DAT_{d}: D1.2 (A), D2.2 (A), R9.1, U1.2 (J), U1.3 (~K)
/DAT_{h}: U4.9, U4.11, U8.11
/DIR.~R: J4.8, U11.1 (G1)
/DIR.~W: J4.7, U12.12
/DS.~U: J4.5, U13.1 (G)
/D_{8}: J4.19, U3.6 (P2), U9.8 (A), U11.18 (Y0)
/D_{9}: J4.20, U3.5 (P1), U9.9 (B), U11.17 (Y1)
/D_{10}: J4.17, U3.4 (P0), U9.10 (C), U11.16 (Y2)
/D_{11}: J4.18, U2.7 (P3), U9.11 (D), U11.15 (Y3)
/D_{12}: J4.15, U2.6 (P2), U9.12 (E), U11.14 (Y4)
/D_{13}: J4.13, U2.5 (P1), U9.13 (F), U11.13 (Y5)
/D_{14}: J4.14, U2.4 (P0), U9.1 (G), U11.12 (Y6)
/D_{15}: J4.11, U1.7 (P3), U9.2 (H), U11.11 (Y7)
/IBSY: J3.2, U10.19 (G2)
/IRQ_{0}: J3.11, U10.11 (Y7)
/IRQ_{1}: J3.12, U10.12 (Y6)
/IRQ_{2}: J3.9, U10.13 (Y5)
/IRQ_{3}: J3.7, U10.14 (Y4)
/IRQ_{4}: J3.8, U10.15 (Y3)
/IRQ_{5}: J3.5, U10.16 (Y2)
/IRQ_{6}: J3.6, U10.17 (Y1)
/IRQ_{7}: J3.3, U10.18 (Y0)
/PORT: U4.2, U4.8, U6.9 (Q), U7.2, U7.10, U10.8 (A6)
/SBSY: R6.1, U6.5 (Q), U8.1, U12.9
/TBSY: C3.2, U5.8, U12.10
/ports_mux/~P_{1}: U4.5, U4.12, U6.8 (~Q), U7.5, U7.13
/shift_registers/D_{q0}: U3.14 (Q1), U11.2 (A0)
/shift_registers/D_{q1}: U3.15 (Q0), U11.3 (A1)
/shift_registers/D_{q2}: U2.12 (Q3), U3.2 (J), U3.3 (~K), U11.4 (A2)
/shift_registers/D_{q3}: U2.13 (Q2), U11.5 (A3)
/shift_registers/D_{q4}: U2.14 (Q1), U11.6 (A4)
/shift_registers/D_{q5}: U2.15 (Q0), U11.7 (A5)
/shift_registers/D_{q6}: U1.12 (Q3), U2.2 (J), U2.3 (~K), U11.8 (A6)
/shift_registers/D_{q7}: U1.13 (Q2), U11.9 (A7)
/shift_registers/EPAR: U1.6 (P2), U9.5 (Even)
/~CLK_{0}: J1.5, Q3.1 (C), R4.2, U7.1, U12.5
/~CLK_{1}: J2.5, Q4.1 (C), R11.2, U7.4, U12.1
/~CLK_{d}: D3.2 (A), D4.2 (A), R17.1, U5.3
/~CLK_{h}: U4.3, U4.6, U8.3, U8.4
/~D_{q}: U3.11 (~Q3), U8.13
/~RCV: U8.8, U10.1 (G1)
/~RES: J3.13, U6.1 (~R)
/~S: U11.19 (G2), U12.13, U13.19 (P=R)
/~W: C4.1, U1.9 (~PE), U2.9 (~PE), U3.9 (~PE), U6.4 (~S), U12.11
GND: B1.2, B2.2, B3.2, B4.2, B5.2, B6.2, B7.2, B8.2, B9.2, B10.2, C1.2, C2.2, J1.3, J1.7, J1.8, J1.9, J2.3, J2.7, J2.8, J2.9, J3.4, J3.10, J3.16, J3.21, J3.22, J3.28, J4.4, J4.10, J4.16, J4.22, J4.28, J4.34, J4.40, J4.46, J4.52, J4.58, M1.1, Q1.3 (E), Q2.3 (E), Q3.3 (E), Q4.3 (E), Q5.3 (E), Q6.3 (E), U1.8 (GND), U2.8 (GND), U3.7 (P3), U3.8 (GND), U4.7 (GND), U5.7 (GND), U6.2 (D), U6.7 (GND), U7.7 (GND), U8.7 (GND), U9.4 (I), U9.7 (GND), U10.2 (A0), U10.4 (A2), U10.5 (A3), U10.6 (A4), U10.7 (A5), U10.10 (GND), U11.10 (GND), U12.7 (GND), U13.3 (R0), U13.5 (R1), U13.7 (R2), U13.9 (R3), U13.10 (GND), U13.12 (R4), U13.14 (R5), U13.15 (P6), U13.16 (R6), U13.18 (R7)
unnamed: C2.1, R10.1, R12.1, U5.9
unnamed: D1.1 (K), U7.11
unnamed: D2.1 (K), U7.8
unnamed: D3.1 (K), U7.3
unnamed: D4.1 (K), U7.6
unnamed: Q1.2 (B), R2.1
unnamed: Q2.2 (B), R3.2
unnamed: C1.1, Q2.1 (C), R6.2, U5.1
unnamed: Q3.2 (B), R5.1
unnamed: Q4.2 (B), R13.1
unnamed: Q5.2 (B), R14.2
unnamed: Q5.1 (C), R12.2
unnamed: Q6.2 (B), R16.1
unnamed: R2.2, U4.10
unnamed: R5.2, U4.1
unnamed: R10.2, U5.5, U8.6
unnamed: R13.2, U4.4
unnamed: R14.1, U5.6
unnamed: R16.2, U4.13
unnamed: U5.10, U8.10
unnamed: U5.12, U8.12
unnamed: U5.2, U5.13, U8.2, U8.9
unnamed: C3.1, R7.2, U5.11, U6.3 (C)
unnamed: R3.1, U6.6 (~Q)
unnamed: C4.2, R8.2, U6.11 (C)
unnamed: U6.13 (~R), U12.6
unnamed: U6.10 (~S), U12.3
unnamed: U12.2, U12.4, U12.8

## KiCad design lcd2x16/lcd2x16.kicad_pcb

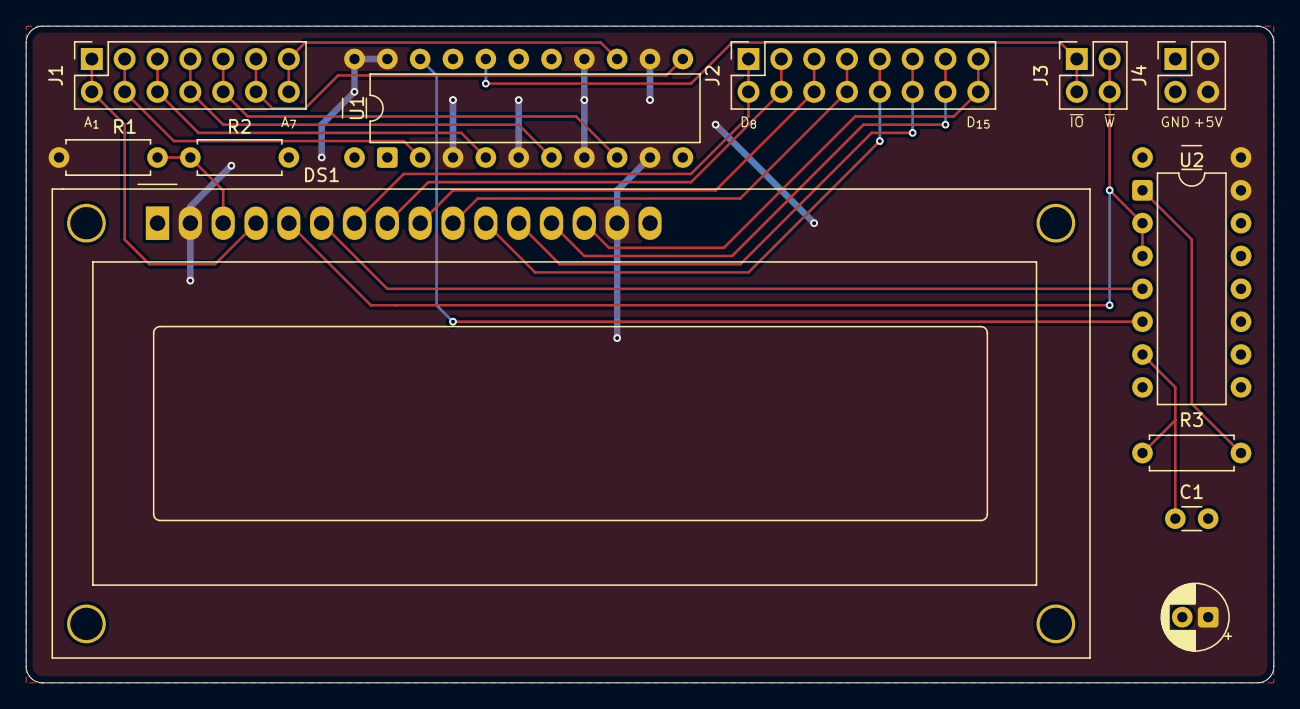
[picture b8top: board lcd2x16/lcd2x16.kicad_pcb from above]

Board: 2 copper layers, 96.5 x 50.8 mm, 14 parts (0 on the bottom side), 24 nets.

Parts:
C1: 220pF; C_Disc_D3.0mm_W1.6mm_P2.54mm
CB1, CB2: C_Disc_D3.0mm_W1.6mm_P7.62mm
CB3: CP_Radial_D5.0mm_P2.00mm
DS1: WC1602A
J1: Aport; PinSocket_2x07_P2.54mm_Vertical
J2: Dport; PinSocket_2x08_P2.54mm_Vertical
J3: Cport; PinSocket_2x02_P2.54mm_Vertical
J4: Pport; PinSocket_2x02_P2.54mm_Vertical
R1: 10k; R_Axial_DIN0207_L6.3mm_D2.5mm_P7.62mm_Horizontal
R2, R3: 1k; R_Axial_DIN0207_L6.3mm_D2.5mm_P7.62mm_Horizontal
U1: 74HC688; DIP-20_W7.62mm
U2: 74HC02; DIP-14_W7.62mm

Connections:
+5V: CB1.1, CB2.1, CB3.1, DS1.2 (VDD), DS1.15 (LED(+)), J4.3, J4.4, R1.1, U1.3 (R0), U1.5 (R1), U1.7 (R2), U1.9 (R3), U1.12 (R4), U1.14 (R5), U1.20 (VCC), U2.14 (VCC)
/E: DS1.6 (E), U2.4
/~S: U1.19 (P=R), U2.5
A_{1}: DS1.4 (RS), J1.1, J1.2
A_{2}: J1.3, J1.4, U1.2 (P0)
A_{3}: J1.5, J1.6, U1.4 (P1)
A_{4}: J1.7, J1.8, U1.6 (P2)
A_{5}: J1.9, J1.10, U1.8 (P3)
A_{6}: J1.11, J1.12, U1.11 (P4)
A_{7}: J1.13, J1.14, U1.13 (P5)
BE.~IO: J3.1, J3.2, U1.17 (P7)
DIR.~W: DS1.5 (R/W), J3.3, J3.4, U2.2, U2.3
D_{8}: DS1.7 (D0), J2.1, J2.2
D_{9}: DS1.8 (D1), J2.3, J2.4
D_{10}: DS1.9 (D2), J2.5, J2.6
D_{11}: DS1.10 (D3), J2.7, J2.8
D_{12}: DS1.11 (D4), J2.9, J2.10
D_{13}: DS1.12 (D5), J2.11, J2.12
D_{14}: DS1.13 (D6), J2.13, J2.14
D_{15}: DS1.14 (D7), J2.15, J2.16
GND: C1.2, CB1.2, CB2.2, CB3.2, DS1.1 (VSS), DS1.16 (LED(-)), J4.1, J4.2, R2.2, U1.1 (G), U1.10 (GND), U1.15 (P6), U1.16 (R6), U1.18 (R7), U2.7 (GND), U2.8, U2.9, U2.11, U2.12
unnamed: C1.1, R3.2, U2.6
unnamed: DS1.3 (VO), R1.2, R2.1
unnamed: R3.1, U2.1

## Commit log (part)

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2025-07-14 finished scheme, footprints not completely assigned yet
2025-07-15 done the pcb layout + added the 1M ram bank project
2025-07-20 updated scheme: - fixed E to P & PRT mapping - swapped root's 04 couple with the 14's of pidreg & statusreg
2025-07-20 routing: progress 1
2025-07-26 apparently the ram was enabled all the time, ram.kicad_sch didn't even require BE.M... like whaaaaaaaa how did i let this happen oh my god sometimes im just braindead.
2025-07-26 connected ram slots to A & D bus
2025-08-03 [scheme] no major changes
2025-08-03 connected A16-23 to atu
2025-08-03 added black pcb png
2025-08-06 first commit: scheme ok [decoder]: - new spv. address space [mmu]: - removed pidreg - switched back to 8Kb mmu rams [ram/peripherals]: - added ground pins to connectors [misc]: - added DMA support - 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
2025-08-06 assigned footprints
2025-10-04 removed SCRM16/10 files
2025-10-04 SF68's first commit
2025-10-04 applied sf68 & ps2 fixes stash from master
2025-10-05 added FOHWL license.
2025-10-05 filled LICENSE
2025-10-05 [ram1M] removed its png, [SF68] removed logic.circ
2025-10-06 added license datamatrix
2025-10-06 [ps2] fixed send request RC constant t must be >= 100us RC was being t, therefore t was actually smaller than 100us RC is now >= 1.28 * 100us (R : 10kohm -> 14.7kohm) t ~= 120us >= 100us
2025-10-06 [ram1M] restored from a SF68 backup
2025-10-06 pngs allowed now!
2026-01-17 1.0.0 commit
2026-01-17 lcd2x16 ready
2026-01-17 ps2 scheme ready
2026-01-31 [vga]: completed the extension using CPLDs
2026-02-01 [vga]: added +12V & GND labels on 12V supply connector
2026-02-01 [ps2]: made pcb design of the new latest schematic
2026-02-07 [ps2]: updated pngs
2026-02-23 [vga]: made a scheme & pcb version with jtag connector included
2026-02-23 [ata]: started
2026-03-09 [ps2] changed fingers footprints
2026-03-09 [vga] added logos + fixed jtag version
2026-04-06 [ps2] can't remember what i've done
2026-04-06 [ata] started, but i think its destined to not go on.
2026-04-06 [lcd2x16] found out the additional logic was useless actually
2026-04-06 [floppy] started
2026-04-06 [vga/jtag] started, fork of original but with jtag port included
2026-04-06 [vga/jtag_fctlines] started, fork of vga/jtag but with 74fct244 as vga line drivers
2026-04-06 [vga/fctlines] started, fork of original but with 74fct244 as vga line drivers
2026-04-06 [vga] added IBM_BIOS bitmap font's 2kb eeprom image + removed some old vga/jtag files
2026-04-06 [vga/fctlines] corrected errors on schematic. Schematic & PCB are NO longer matching.
